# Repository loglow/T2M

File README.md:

See: https://forum.pjrc.com/threads/58795-T2M-an-Embeddable-Teensy-Module-(WIP)

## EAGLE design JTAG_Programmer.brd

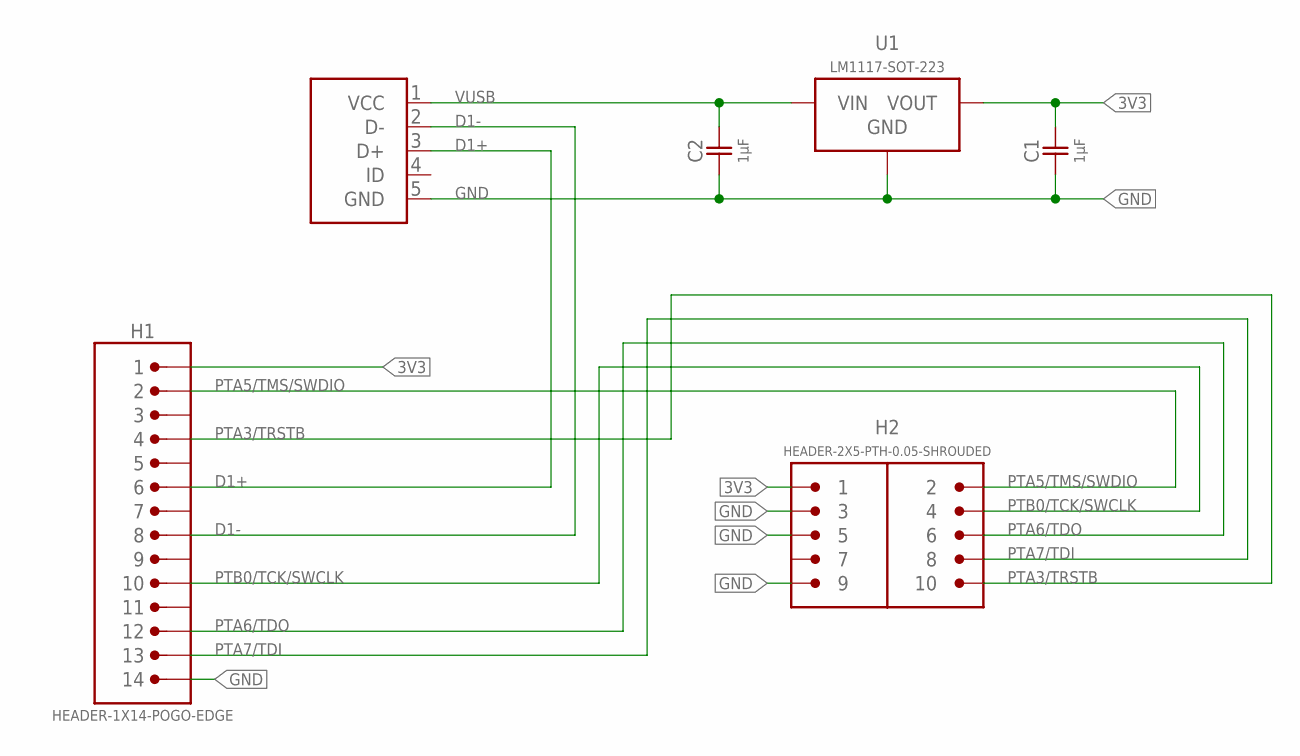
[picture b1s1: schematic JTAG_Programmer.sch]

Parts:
C1, C2: 1µF; 0805-NP
H1: HEADER-1X14-POGO-EDGE; 2X7-1.27MM-POGO-EDGE
H2: HEADER-2X5-PTH-0.05-SHROUDED; PTH-0.05-2X5-SHROUDED
J1: USB-5-MICRO-B; USB-MICRO-B
U1: LM1117-SOT-223; SOT-223

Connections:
3V3: C1.2, H1.1, H2.1, U1.2 (VOUT), U1.4 (VOUT)
D1+: H1.6, J1.3 (D+)
D1-: H1.8, J1.2 (D-)
GND: C1.1, C2.1, H1.14, H2.3, H2.5, H2.9, J1.5 (GND), U1.1 (GND)
PTA3/TRSTB: H1.4, H2.10
PTA5/TMS/SWDIO: H1.2, H2.2
PTA6/TDO: H1.12, H2.6
PTA7/TDI: H1.13, H2.8
PTB0/TCK/SWCLK: H1.10, H2.4
VUSB: C2.2, J1.1 (VCC), U1.3 (VIN)

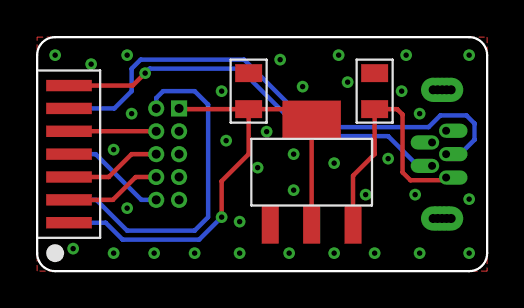
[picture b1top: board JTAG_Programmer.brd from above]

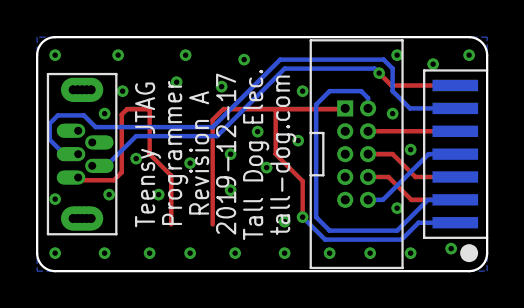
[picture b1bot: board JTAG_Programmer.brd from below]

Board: 2 copper layers, 25.0 x 13.0 mm, 6 parts (2 on the bottom side), 10 nets.

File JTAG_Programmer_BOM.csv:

Ref,Qty,Desc,Mfg,MPN,Digi-Key
C1 C2,2,1µF ±10% 16V Ceramic Capacitor X7R 0805 (2012 Metric),Yageo,CC0805KKX7R7BB105,311-1365-1-ND
H1,1,14 Position Spring Piston Connector Through Hole,Mill-Max,855-22-014-10-001101,855-22-014-10-001101-ND
H2,1,"Connector Header Through Hole 10 position 0.050"" (1.27mm)",CNC Tech,3220-10-0100-00,1175-1627-ND
J1,1,USB - micro B USB 2.0 Receptacle Connector 5 Position Through Hole,GCT,USB3131-30-0230-A,2073-USB3131-30-0230-ACT-ND
U1,1,Linear Voltage Regulator IC 1 Output 800mA SOT-223-4,Texas Instruments,LM1117MPX-3.3/NOPB,LM1117MPX-3.3/NOPBCT-ND

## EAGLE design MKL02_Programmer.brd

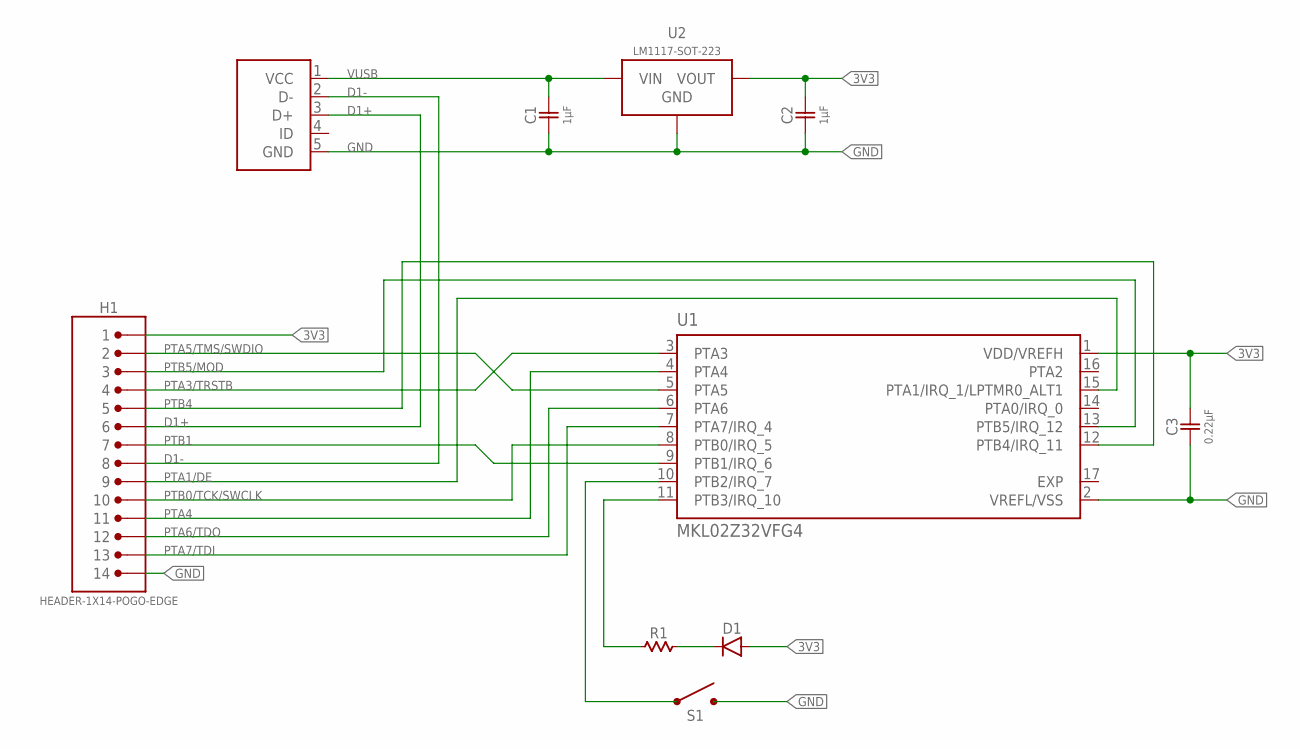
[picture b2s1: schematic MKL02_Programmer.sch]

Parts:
C1, C2: 1µF; 0805-NP
C3: 0.22µF; 0805-NP
D1: DIODE-0805; 0805-P
H1: HEADER-1X14-POGO-EDGE; 2X7-1.27MM-POGO-EDGE
J1: USB-5-MICRO-B; USB-MICRO-B
R1: RESISTOR-0805; 0805-NP
S1: SPST-6X6; BUTTON-EVQQ2
U1: MKL02Z32VFG4; QFN50P300X300X65-17N
U2: LM1117-SOT-223; SOT-223

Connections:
3V3: C2.2, C3.2, D1.A, H1.1, U1.1 (VDD/VREFH), U2.2 (VOUT), U2.4 (VOUT)
D1+: H1.6, J1.3 (D+)
D1-: H1.8, J1.2 (D-)
EXP: U1.17 (EXP)
GND: C1.1, C2.1, C3.1, H1.14, J1.5 (GND), S1.B1 (2), S1.B2 (2), U1.2 (VREFL/VSS), U2.1 (GND)
unnamed: S1.A1 (1), S1.A2 (1), U1.10 (PTB2/IRQ_7)
unnamed: R1.1, U1.11 (PTB3/IRQ_10)
unnamed: D1.K (C), R1.2
PTA1/DE: H1.9, U1.15 (PTA1/IRQ_1/LPTMR0_ALT1)
PTA3/TRSTB: H1.4, U1.3 (PTA3)
PTA4: H1.11, U1.4 (PTA4)
PTA5/TMS/SWDIO: H1.2, U1.5 (PTA5)
PTA6/TDO: H1.12, U1.6 (PTA6)
PTA7/TDI: H1.13, U1.7 (PTA7/IRQ_4)
PTB0/TCK/SWCLK: H1.10, U1.8 (PTB0/IRQ_5)
PTB1: H1.7, U1.9 (PTB1/IRQ_6)
PTB4: H1.5, U1.12 (PTB4/IRQ_11)
PTB5/MOD: H1.3, U1.13 (PTB5/IRQ_12)
VUSB: C1.2, J1.1 (VCC), U2.3 (VIN)

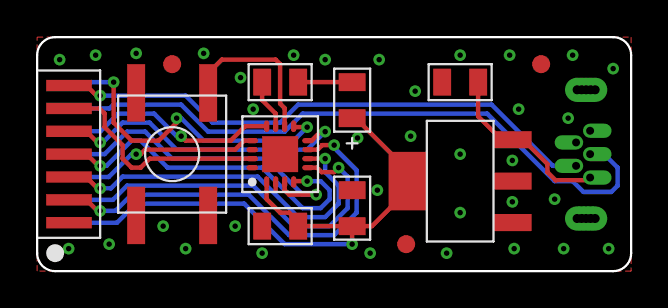
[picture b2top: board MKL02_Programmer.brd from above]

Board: 2 copper layers, 33.0 x 13.0 mm, 13 parts (1 on the bottom side), 18 nets.

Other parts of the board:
U$1, U$2, U$3: FIDUCIAL

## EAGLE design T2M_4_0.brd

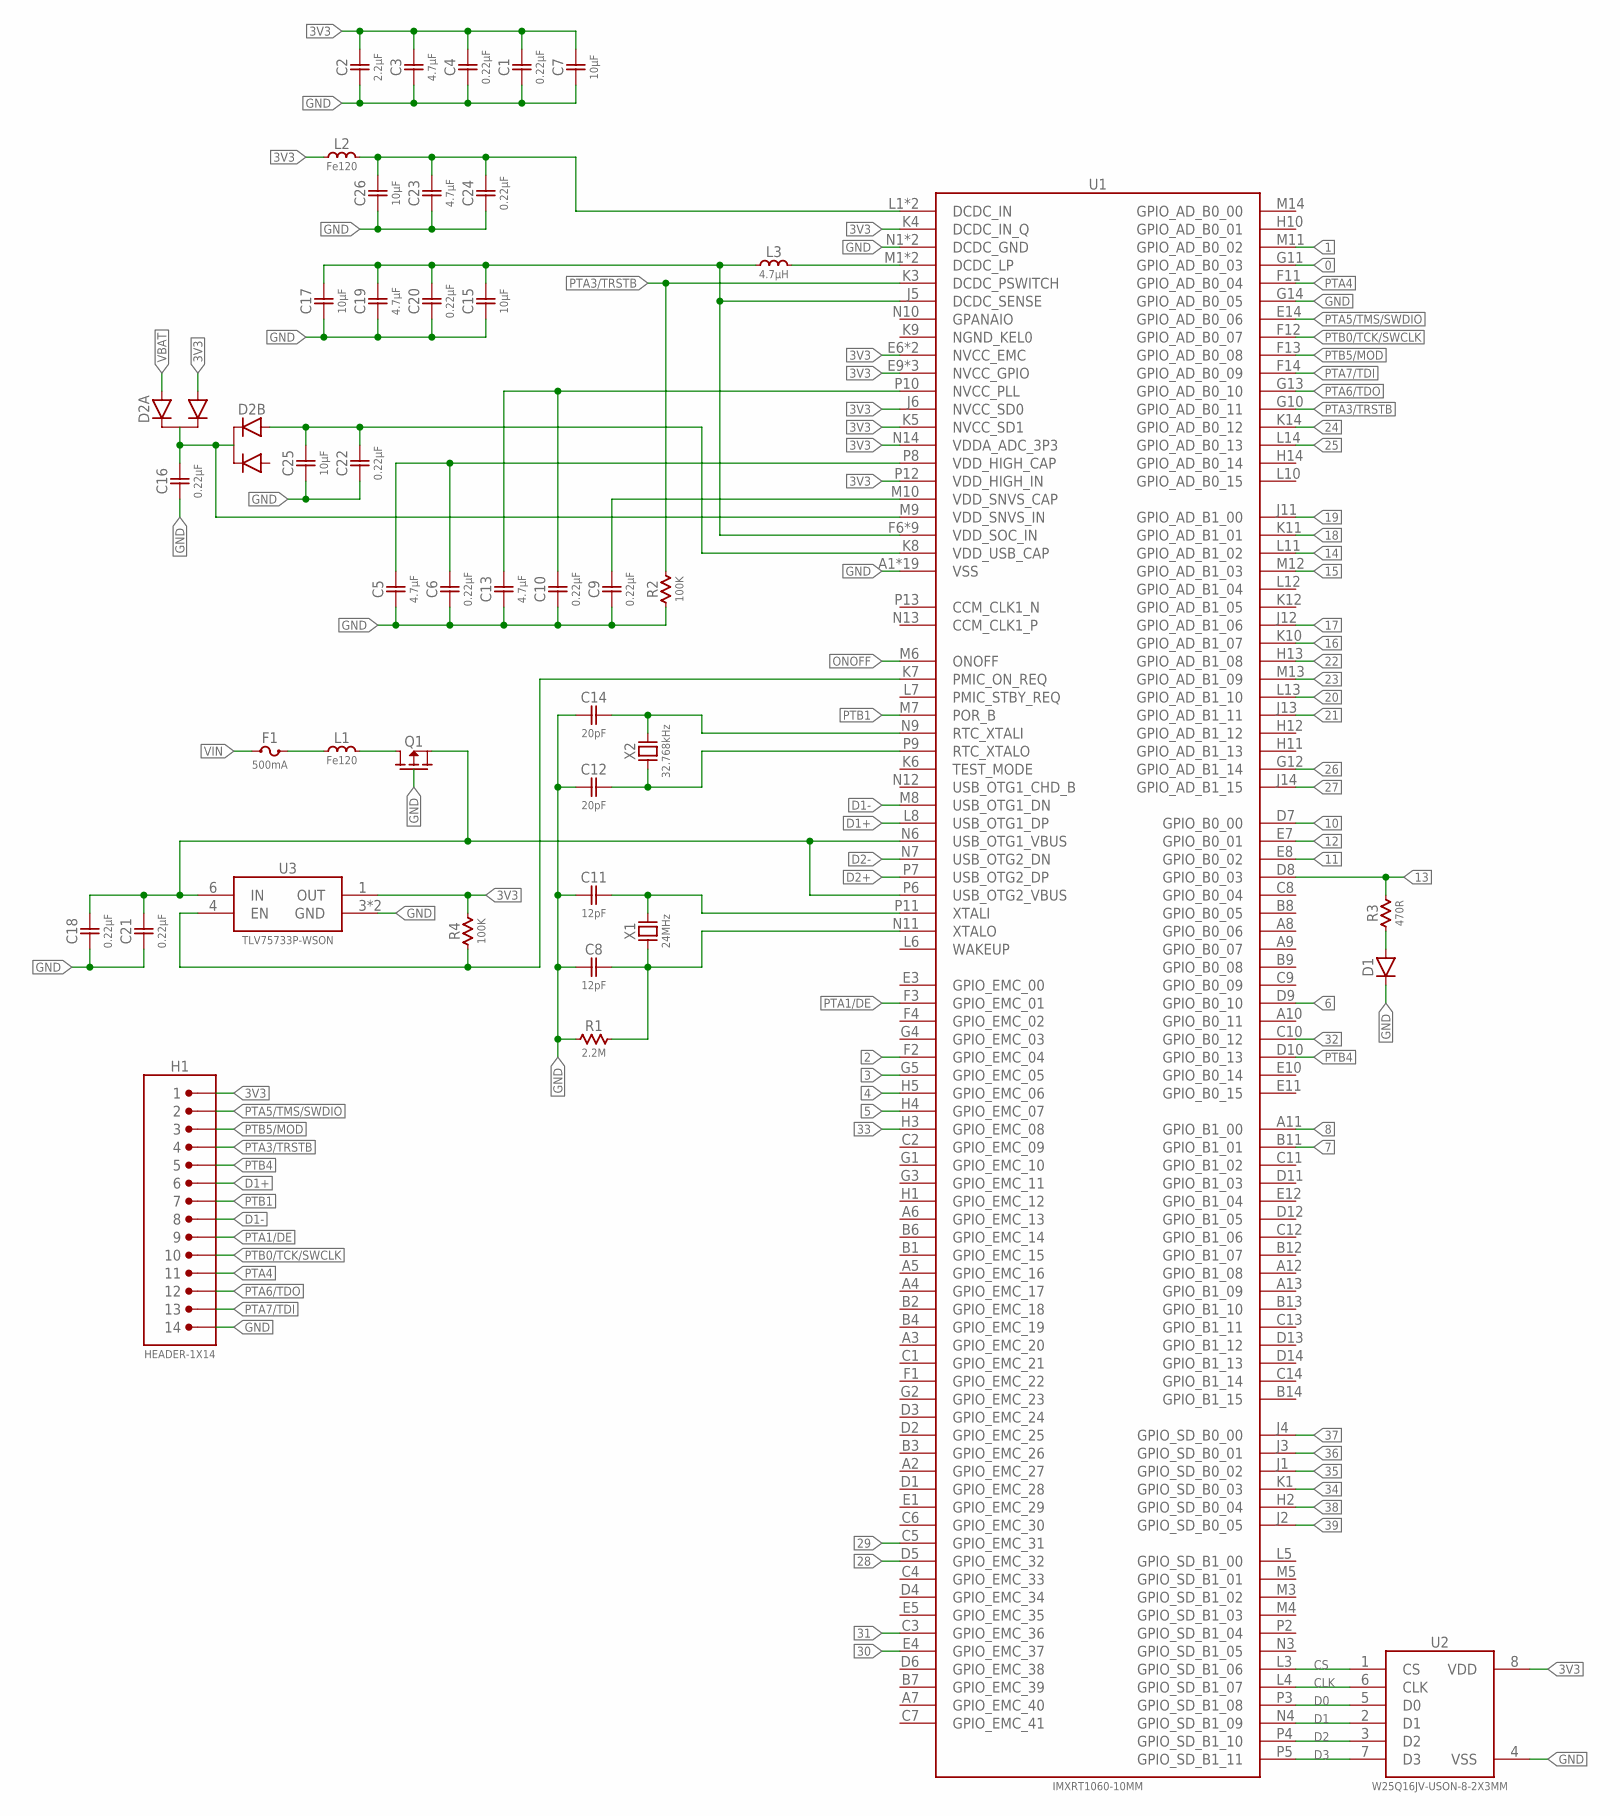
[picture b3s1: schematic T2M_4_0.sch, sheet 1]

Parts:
C1, C4, C6, C9, C10, C16, C18, C20, C21, C22, C24: 0.22µF; 0402-NP
C2: 2.2µF; 0402-NP
C3, C5, C13, C19, C23: 4.7µF; 0402-NP
C7, C15, C17, C25, C26: 10µF; 0603-NP
C8, C11: 12pF; 0402-NP
C12, C14: 20pF; 0402-NP
D1: DIODE-0402; 0402-P
D2: BAT54C-2-SOT-666; SOT-666
F1: 500mA; 0603-NP
H1: HEADER-1X14; 2X7-1.27MM
L1, L2: Fe120; 0402-NP
L3: 4.7µH; 0603-NP
Q1: MOSFET-P; SOT-23
R1: 2.2M; 0402-NP
R2, R4: 100K; 0402-NP
R3: 470R; 0402-NP
U1: IMXRT1060-10MM; BGA-196-10MM
U2: W25Q16JV-USON-8-2X3MM; USON-8-2X3MM
U3: TLV75733P-WSON; WSON-6
X1: 24MHz; CRYSTAL-2X1.6MM
X2: 32.768kHz; CRYSTAL-2X1.2MM

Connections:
0: U1.G11 (GPIO_AD_B0_03); also elsewhere on the board
1: U1.M11 (GPIO_AD_B0_02); also elsewhere on the board
2: U1.F2 (GPIO_EMC_04); also elsewhere on the board
3: U1.G5 (GPIO_EMC_05); also elsewhere on the board
3V3: C1.2, C2.2, C3.2, C4.2, C7.2, D2.2 (A2), H1.1, L2.1, R4.2, U1.E6 (NVCC_EMC), U1.E9 (NVCC_GPIO), U1.F5 (NVCC_EMC), U1.F10 (NVCC_GPIO), U1.J6 (NVCC_SD0), U1.J10 (NVCC_GPIO), U1.K4 (DCDC_IN_Q), U1.K5 (NVCC_SD1), U1.N14 (VDDA_ADC_3P3), U1.P12 (VDD_HIGH_IN), U2.8 (VDD), U3.1 (OUT); also elsewhere on the board
4: U1.H5 (GPIO_EMC_06); also elsewhere on the board
5: U1.H4 (GPIO_EMC_07); also elsewhere on the board
6: U1.D9 (GPIO_B0_10); also elsewhere on the board
7: U1.B11 (GPIO_B1_01); also elsewhere on the board
8: U1.A11 (GPIO_B1_00); also elsewhere on the board
10: U1.D7 (GPIO_B0_00); also elsewhere on the board
11: U1.E8 (GPIO_B0_02); also elsewhere on the board
12: U1.E7 (GPIO_B0_01); also elsewhere on the board
13: R3.2, U1.D8 (GPIO_B0_03); also elsewhere on the board
14: U1.L11 (GPIO_AD_B1_02); also elsewhere on the board
15: U1.M12 (GPIO_AD_B1_03); also elsewhere on the board
16: U1.K10 (GPIO_AD_B1_07); also elsewhere on the board
17: U1.J12 (GPIO_AD_B1_06); also elsewhere on the board
18: U1.K11 (GPIO_AD_B1_01); also elsewhere on the board
19: U1.J11 (GPIO_AD_B1_00); also elsewhere on the board
20: U1.L13 (GPIO_AD_B1_10); also elsewhere on the board
21: U1.J13 (GPIO_AD_B1_11); also elsewhere on the board
22: U1.H13 (GPIO_AD_B1_08); also elsewhere on the board
23: U1.M13 (GPIO_AD_B1_09); also elsewhere on the board
24: U1.K14 (GPIO_AD_B0_12); also elsewhere on the board
25: U1.L14 (GPIO_AD_B0_13); also elsewhere on the board
26: U1.G12 (GPIO_AD_B1_14); also elsewhere on the board
27: U1.J14 (GPIO_AD_B1_15); also elsewhere on the board
28: U1.D5 (GPIO_EMC_32); also elsewhere on the board
29: U1.C5 (GPIO_EMC_31); also elsewhere on the board
30: U1.E4 (GPIO_EMC_37); also elsewhere on the board
31: U1.C3 (GPIO_EMC_36); also elsewhere on the board
32: U1.C10 (GPIO_B0_12); also elsewhere on the board
33: U1.H3 (GPIO_EMC_08); also elsewhere on the board
34: U1.K1 (GPIO_SD_B0_03); also elsewhere on the board
35: U1.J1 (GPIO_SD_B0_02); also elsewhere on the board
36: U1.J3 (GPIO_SD_B0_01); also elsewhere on the board
37: U1.J4 (GPIO_SD_B0_00); also elsewhere on the board
38: U1.H2 (GPIO_SD_B0_04); also elsewhere on the board
39: U1.J2 (GPIO_SD_B0_05); also elsewhere on the board
CLK: U1.L4 (GPIO_SD_B1_07), U2.6 (CLK)
CS: U1.L3 (GPIO_SD_B1_06), U2.1 (CS)
D0: U1.P3 (GPIO_SD_B1_08), U2.5 (D0)
D1: U1.N4 (GPIO_SD_B1_09), U2.2 (D1)
D1+: H1.6, U1.L8 (USB_OTG1_DP); also elsewhere on the board
D1-: H1.8, U1.M8 (USB_OTG1_DN); also elsewhere on the board
D2: U1.P4 (GPIO_SD_B1_10), U2.3 (D2)
D2+: U1.P7 (USB_OTG2_DP); also elsewhere on the board
D2-: U1.N7 (USB_OTG2_DN); also elsewhere on the board
D3: U1.P5 (GPIO_SD_B1_11), U2.7 (D3)
GND: C1.1, C2.1, C3.1, C4.1, C5.1, C6.1, C7.1, C8.1, C9.1, C10.1, C11.1, C12.1, C13.1, C14.1, C15.1, C16.1, C17.1, C18.1, C19.1, C20.1, C21.1, C22.1, C23.1, C24.1, C25.1, C26.1, D1.C, H1.14, Q1.1 (G), R1.1, R2.1, U1.A1 (VSS), U1.A14 (VSS), U1.B5 (VSS), U1.B10 (VSS), U1.E2 (VSS), U1.E13 (VSS), U1.G7 (VSS), U1.G8 (VSS), U1.G14 (GPIO_AD_B0_05), U1.H7 (VSS), U1.H8 (VSS), U1.J7 (VSS), U1.J8 (VSS), U1.K2 (VSS), U1.K13 (VSS), U1.L9 (VSS), U1.N1 (DCDC_GND), U1.N2 (DCDC_GND), U1.N5 (VSS), U1.N8 (VSS), U1.P1 (VSS), U1.P14 (VSS), U2.4 (VSS), U3.3 (GND), U3.7 (GND); also elsewhere on the board
unnamed: C11.2, U1.P11 (XTALI), X1.3 (2)
unnamed: C8.2, R1.2, U1.N11 (XTALO), X1.1
unnamed: C14.2, U1.N9 (RTC_XTALI), X2.2
unnamed: C12.2, U1.P9 (RTC_XTALO), X2.1
unnamed: D1.A, R3.1
unnamed: C18.2, C21.2, Q1.2 (S), U1.N6 (USB_OTG1_VBUS), U1.P6 (USB_OTG2_VBUS), U3.6 (IN)
unnamed: R4.1, U1.K7 (PMIC_ON_REQ), U3.4 (EN)
unnamed: C22.2, C25.2, D2.4 (A1), U1.K8 (VDD_USB_CAP)
unnamed: L3.2, U1.M1 (DCDC_LP), U1.M2 (DCDC_LP)
unnamed: C23.2, C24.2, C26.2, L2.2, U1.L1 (DCDC_IN), U1.L2 (DCDC_IN)
unnamed: C15.2, C17.2, C19.2, C20.2, L3.1, U1.F6 (VDD_SOC_IN), U1.F7 (VDD_SOC_IN), U1.F8 (VDD_SOC_IN), U1.F9 (VDD_SOC_IN), U1.G6 (VDD_SOC_IN), U1.G9 (VDD_SOC_IN), U1.H6 (VDD_SOC_IN), U1.H9 (VDD_SOC_IN), U1.J5 (DCDC_SENSE), U1.J9 (VDD_SOC_IN)
unnamed: C16.2, D2.3 (CC), D2.6 (CC), U1.M9 (VDD_SNVS_IN)
unnamed: L1.2, Q1.3 (D)
unnamed: F1.2, L1.1
unnamed: C5.2, C6.2, U1.P8 (VDD_HIGH_CAP)
unnamed: C10.2, C13.2, U1.P10 (NVCC_PLL)
unnamed: C9.2, U1.M10 (VDD_SNVS_CAP)
ONOFF: U1.M6 (ONOFF); also elsewhere on the board
PTA1/DE: H1.9, U1.F3 (GPIO_EMC_01); also elsewhere on the board
PTA3/TRSTB: H1.4, R2.2, U1.G10 (GPIO_AD_B0_11), U1.K3 (DCDC_PSWITCH); also elsewhere on the board
PTA4: H1.11, U1.F11 (GPIO_AD_B0_04); also elsewhere on the board
PTA5/TMS/SWDIO: H1.2, U1.E14 (GPIO_AD_B0_06); also elsewhere on the board
PTA6/TDO: H1.12, U1.G13 (GPIO_AD_B0_10); also elsewhere on the board
PTA7/TDI: H1.13, U1.F14 (GPIO_AD_B0_09); also elsewhere on the board
PTB0/TCK/SWCLK: H1.10, U1.F12 (GPIO_AD_B0_07); also elsewhere on the board
PTB1: H1.7, U1.M7 (POR_B); also elsewhere on the board
PTB4: H1.5, U1.D10 (GPIO_B0_13); also elsewhere on the board
PTB5/MOD: H1.3, U1.F13 (GPIO_AD_B0_08); also elsewhere on the board
VBAT: D2.1 (A1); also elsewhere on the board
VIN: F1.1; also elsewhere on the board

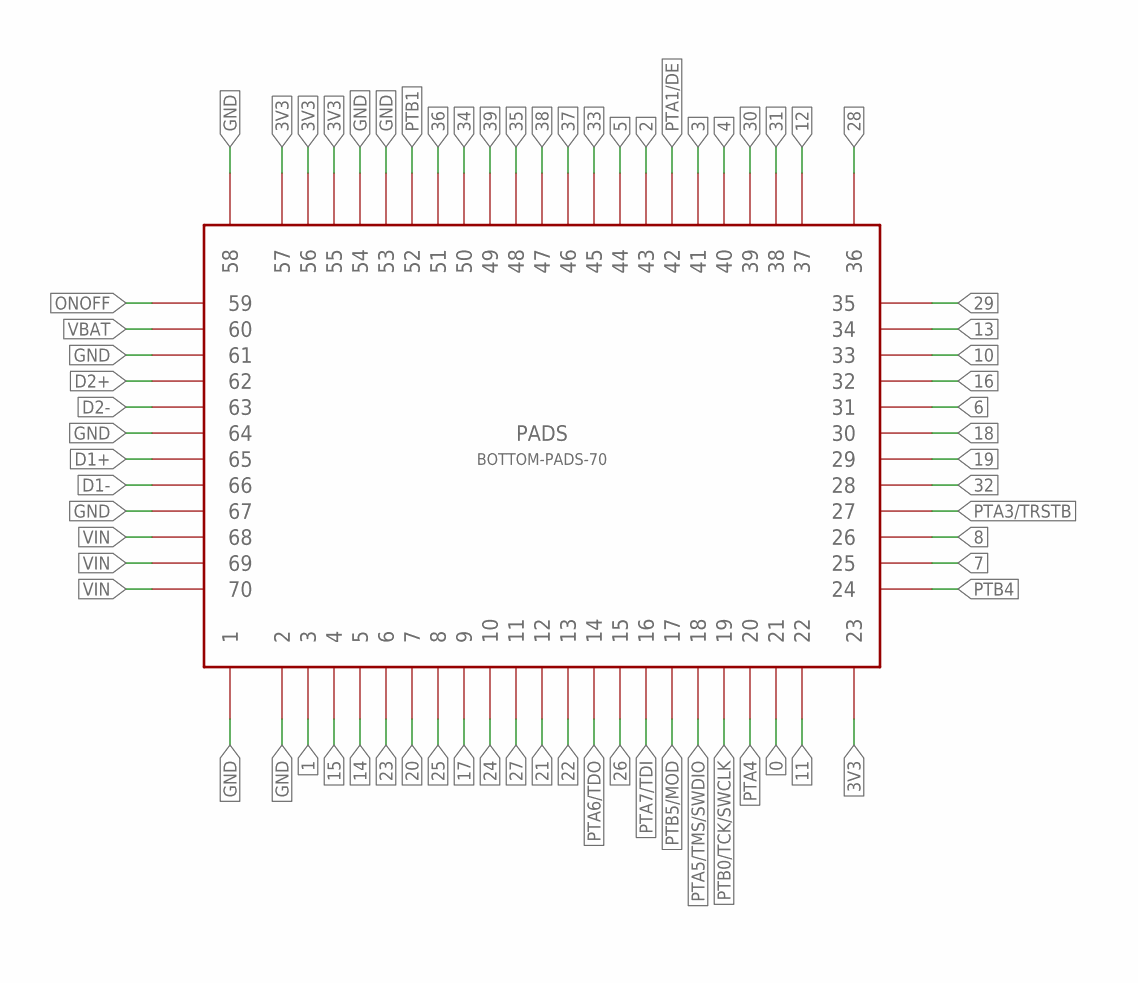
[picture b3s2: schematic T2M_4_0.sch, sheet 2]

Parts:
PADS: BOTTOM-PADS-70

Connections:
0: PADS.21; also elsewhere on the board
1: PADS.3; also elsewhere on the board
2: PADS.43; also elsewhere on the board
3: PADS.41; also elsewhere on the board
3V3: PADS.23, PADS.55, PADS.56, PADS.57; also elsewhere on the board
4: PADS.40; also elsewhere on the board
5: PADS.44; also elsewhere on the board
6: PADS.31; also elsewhere on the board
7: PADS.25; also elsewhere on the board
8: PADS.26; also elsewhere on the board
10: PADS.33; also elsewhere on the board
11: PADS.22; also elsewhere on the board
12: PADS.37; also elsewhere on the board
13: PADS.34; also elsewhere on the board
14: PADS.5; also elsewhere on the board
15: PADS.4; also elsewhere on the board
16: PADS.32; also elsewhere on the board
17: PADS.9; also elsewhere on the board
18: PADS.30; also elsewhere on the board
19: PADS.29; also elsewhere on the board
20: PADS.7; also elsewhere on the board
21: PADS.12; also elsewhere on the board
22: PADS.13; also elsewhere on the board
23: PADS.6; also elsewhere on the board
24: PADS.10; also elsewhere on the board
25: PADS.8; also elsewhere on the board
26: PADS.15; also elsewhere on the board
27: PADS.11; also elsewhere on the board
28: PADS.36; also elsewhere on the board
29: PADS.35; also elsewhere on the board
30: PADS.39; also elsewhere on the board
31: PADS.38; also elsewhere on the board
32: PADS.28; also elsewhere on the board
33: PADS.45; also elsewhere on the board
34: PADS.50; also elsewhere on the board
35: PADS.48; also elsewhere on the board
36: PADS.51; also elsewhere on the board
37: PADS.46; also elsewhere on the board
38: PADS.47; also elsewhere on the board
39: PADS.49; also elsewhere on the board
D1+: PADS.65; also elsewhere on the board
D1-: PADS.66; also elsewhere on the board
D2+: PADS.62; also elsewhere on the board
D2-: PADS.63; also elsewhere on the board
GND: PADS.1, PADS.2, PADS.53, PADS.54, PADS.58, PADS.61, PADS.64, PADS.67; also elsewhere on the board
ONOFF: PADS.59; also elsewhere on the board
PTA1/DE: PADS.42; also elsewhere on the board
PTA3/TRSTB: PADS.27; also elsewhere on the board
PTA4: PADS.20; also elsewhere on the board
PTA5/TMS/SWDIO: PADS.18; also elsewhere on the board
PTA6/TDO: PADS.14; also elsewhere on the board
PTA7/TDI: PADS.16; also elsewhere on the board
PTB0/TCK/SWCLK: PADS.19; also elsewhere on the board
PTB1: PADS.52; also elsewhere on the board
PTB4: PADS.24; also elsewhere on the board
PTB5/MOD: PADS.17; also elsewhere on the board
VBAT: PADS.60; also elsewhere on the board
VIN: PADS.68, PADS.69, PADS.70; also elsewhere on the board

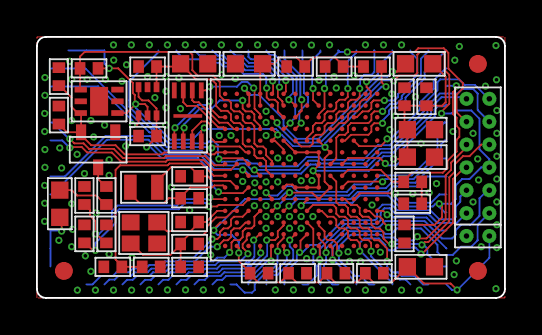
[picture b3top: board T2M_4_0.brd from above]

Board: 2 copper layers, 26.0 x 14.5 mm, 47 parts (0 on the bottom side), 81 nets.

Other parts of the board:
FID1, FID2, FID3: FIDUCIAL

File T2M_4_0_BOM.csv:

Ref,Qty,Desc,Mfg,MPN,Digi-Key
C1 C4 C6 C9 C10 C16 C18 C20 C21 C22 C24,11,0.22µF ±10% 16V Ceramic Capacitor X7R 0402 (1005 Metric),Samsung,CL05B224KO5NNNC,1276-1176-1-ND
C2,1,2.2µF ±20% 10V Ceramic Capacitor X5R 0402 (1005 Metric),Murata,GRM155R61A225ME95D,490-10452-1-ND
C3 C5 C13 C19 C23,5,4.7µF ±20% 10V Ceramic Capacitor X5R 0402 (1005 Metric),Murata,GRM155R61A475MEAAD,490-14306-1-ND
C7 C15 C17 C25 C26,5,10µF ±20% 16V Ceramic Capacitor X5R 0603 (1608 Metric),Murata,GRM188R61C106MA73D,490-7201-1-ND
C8 C11,2,"12pF ±5% 50V Ceramic Capacitor C0G, NP0 0402 (1005 Metric)",Yageo,CC0402JRNPO9BN120,311-1016-1-ND
C12 C14,2,"20pF ±5% 50V Ceramic Capacitor C0G, NP0 0402 (1005 Metric)",Yageo,CC0402JRNPO9BN200,311-1417-1-ND
D1,1,Orange 605nm LED Indication - Discrete 2V 0402 (1005 Metric),Vishay,VLMO1500-GS08,VLMO1500-GS08CT-ND
D2,1,"Diode Array 2 Pair Common Cathode Schottky 30V 200mA (DC) Surface Mount SOT-563, SOT-666",Nexperia,"BAT54CV,115",1727-3568-1-ND
F1,1,"Polymeric PTC Resettable Fuse 9V 200mA Ih Surface Mount 0603 (1608 Metric), Concave",Bourns,MF-FSMF020X-2,MF-FSMF020X-2CT-ND
L1 L2,2,120 Ohms @ 100MHz 1 Power Line Ferrite Bead 0402 (1005 Metric) 1.3A 91mOhm,Taiyo Yuden,BKP1005TS121-T,587-3014-1-ND
L3,1,4.7µH Shielded Multilayer Inductor 400mA 320mOhm 0603 (1608 Metric),TDK,MLZ1608N4R7LT000,445-9286-1-ND
Q1,1,P-Channel 20V 4.2A (Ta) 1.4W (Ta) Surface Mount SOT-23,Diodes Inc,DMG2305UX-13,DMG2305UX-13DICT-ND
R1,1,"2.2 MOhms ±5% 0.063W, 1/16W Chip Resistor 0402 (1005 Metric) Moisture Resistant Thick Film",Yageo,RC0402JR-072M2L,YAG3292CT-ND
R2 R4,2,"100 kOhms ±1% 0.063W, 1/16W Chip Resistor 0402 (1005 Metric) Moisture Resistant Thick Film",Yageo,RC0402FR-07100KL,311-100KLRCT-ND
R3,1,"470 Ohms ±1% 0.063W, 1/16W Chip Resistor 0402 (1005 Metric) Moisture Resistant Thick Film",Yageo,RC0402FR-07470RL,311-470LRCT-ND
U1,1,ARM® Cortex®-M7 RT1060 Microcontroller IC 32-Bit 600MHz  External Program Memory 196-MAPBGA (10x10),NXP,MIMXRT1062DVL6A,568-14668-ND
U2,1,3V 16M-Bit Serial Flash Memory With Dual/Quad SPI,Winbond,W25Q16JVUXIQ,N/A (search Octopart)
U3,1,Linear Voltage Regulator IC 1 Output 1A 6-WSON (2x2),Texas Instruments,TLV75733PDRVR,296-49281-1-ND
X1,1,"24MHz ±10ppm Crystal 8pF 100 Ohms 4-SMD, No Lead",Abracon,ABM11W-24.0000MHZ-8-B1U-T3,535-13834-1-ND
X2,1,"32.768kHz ±20ppm Crystal 12.5pF 90 kOhms 2-SMD, No Lead",Epson,FC-12M 32.7680KA-A5,SER4080CT-ND
